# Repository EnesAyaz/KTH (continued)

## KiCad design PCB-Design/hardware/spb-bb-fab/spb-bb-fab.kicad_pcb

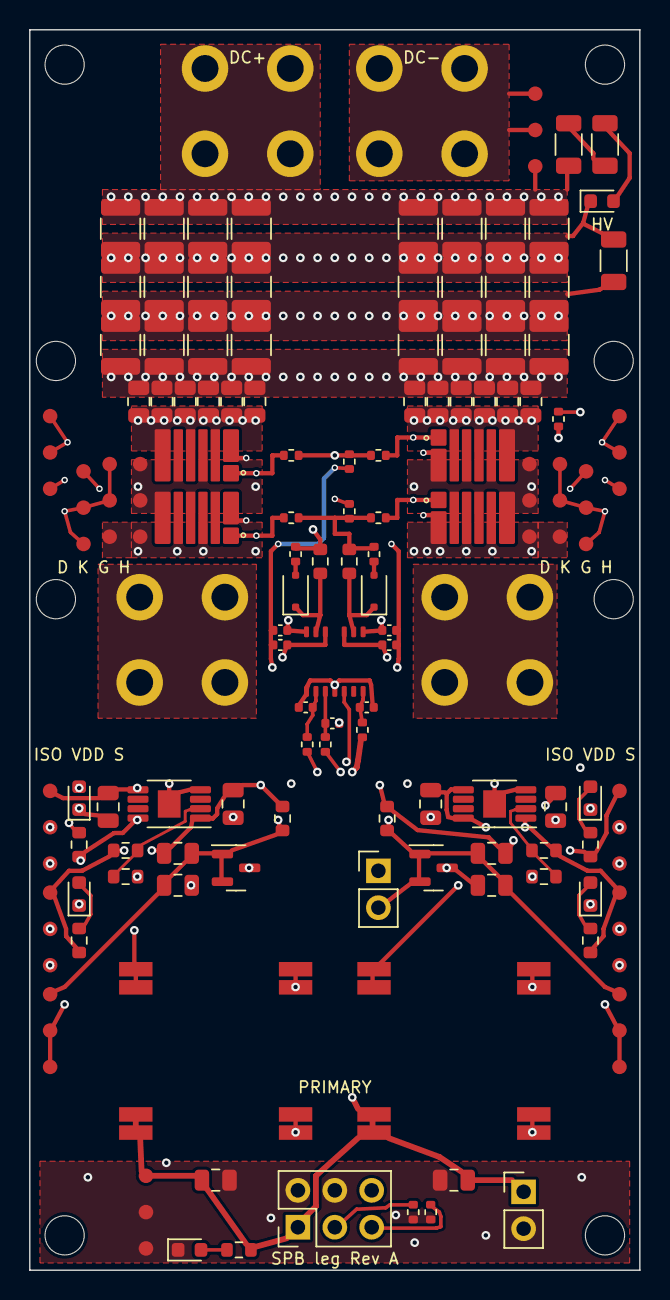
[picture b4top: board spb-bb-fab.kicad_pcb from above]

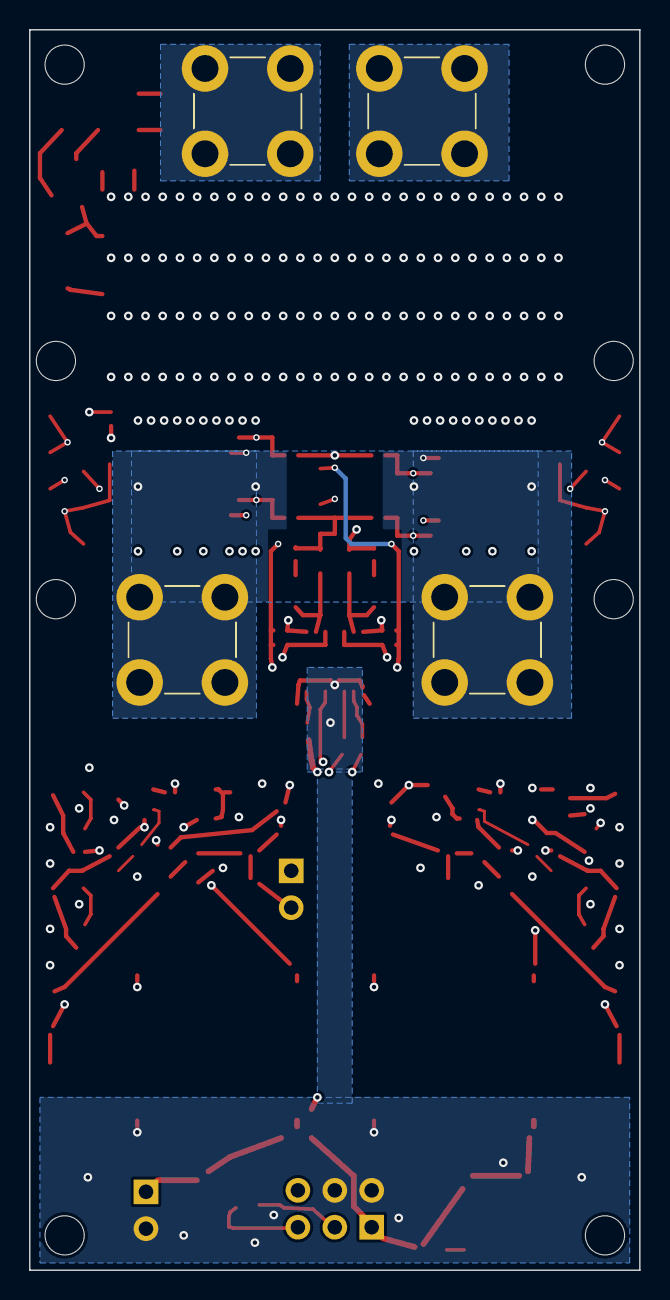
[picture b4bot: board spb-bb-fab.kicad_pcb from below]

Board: 4 copper layers, 42.0 x 85.4 mm, 134 parts (4 on the bottom side), 37 nets.

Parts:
C1, C2, C3, C4, C5, C6, C7, C8, C9, C10, C11, C12: 1uF 100V X7S; C_0805_2012Metric_TightCrtYd
C13, C14, C15, C16, C17, C18, C19, C20, C21, C22, C23, C24, C25, C26, C27, C28, C29, C30, C31, C32, C33, C34, C35, C36: 10uF 100V X7S; C_1210_3225Metric_TightCrtYd
C100, C101, C102, C103: 1uF 16V X7R 0402; C_0402_1005Metric
C104, C105: 100pF C0G 0402; C_0402_1005Metric
C106: 22nF 25V X7R 0402; C_0402_1005Metric
C107, C112: 4.7uF 25V X7R 0805; C_0805_2012Metric
C108, C113: 10uF 16V X7R 0805; C_0805_2012Metric
C109, C110, C114, C115: 4.7uF 16V X7R 0805; C_0805_2012Metric
C111, C116: 4.7uF 25V X7R 0805 (12 V in); C_0805_2012Metric
D1, D2: PMEG3020EJ; D_SOD-323F
D3: green 0603 (ISO A); LED_0603_1608Metric
D4: green 0603 (VDD A); LED_0603_1608Metric
D5: green 0603 (ISO B); LED_0603_1608Metric
D6: green 0603 (VDD B); LED_0603_1608Metric
D7: green 0603 (12 V); LED_0603_1608Metric
D8: red 0603 (DC link present); LED_0603_1608Metric
H1, H2, H3, H4: M2.5 insulated; MountingHole_2.7mm_M2.5
H5, H6, H7, H8: M2.5 heatsink; MountingHole_2.7mm_M2.5
HS1: Fischer LAM 4 K 50 12 + spreader; HS_LAM4K5012_assembly
J1: DC+; Wuerth_REDCUBE-THR_WP-THRBU_74650174_THR
J2: DC-; Wuerth_REDCUBE-THR_WP-THRBU_74650174_THR
J3, J4: AC; Wuerth_REDCUBE-THR_WP-THRBU_74650174_THR
J5: 1:+12V 2:GND 3:PWM_H 4:GND 5:PWM_L 6:DIS; PinHeader_2x03_P2.54mm_Vertical
J6: 1:NTC 2:DC- (LS domain!); PinHeader_1x02_P2.54mm_Vertical
J7: FAN 12V: 1 +12V, 2 GND; PinHeader_1x02_P2.54mm_Vertical
PS1, PS2: MGN1S1208MC; Murata_MGN1_SMD
Q1, Q2, Q3, Q4: EPC2361
R1: 0R5 1% (gate HL); R_0402_1005Metric
R2: 0R5 1% (gate HR); R_0402_1005Metric
R3: 0R5 1% (gate LL); R_0402_1005Metric
R4: 0R5 1% (gate LR); R_0402_1005Metric
R5: 0R75 1% (R_ON,A); R_0603_1608Metric
R6: 0R (R_OFF,A); R_0402_1005Metric
R7: 0R75 1% (R_ON,B); R_0603_1608Metric
R8: 0R (R_OFF,B); R_0402_1005Metric
R9: 47R 1% (INA); R_0402_1005Metric
R10: 47R 1% (INB); R_0402_1005Metric
R11: 3k 1% (RVDDI); R_0402_1005Metric
R12, R15: 102k 1%; R_0603_1608Metric
R13, R16: 23.7k 1%; R_0603_1608Metric
R14, R17: 2.2k 1% (shunt bias); R_0603_1608Metric
R30, R32: 2.7k (LED); R_0603_1608Metric
R31, R33: 1.8k (LED); R_0603_1608Metric
R34: 4.7k (LED); R_0603_1608Metric
R35: 10k (PWM_H pull-down); R_0402_1005Metric
R36: 10k (PWM_L pull-down); R_0402_1005Metric
R37, R38: 68k 1206 (HV LED); R_1206_3216Metric
R39: 100k 1206 (bleeder); R_1206_3216Metric
R41: 10k 1% (HS gate pull-down); R_0402_1005Metric
R42: 10k 1% (LS gate pull-down); R_0402_1005Metric
RT1: NTC 10k B3380; R_0402_1005Metric
TP1: D: Vds Q3; Probe_2Sig1Gnd_2.5_5.0
TP2: K: vKS Q3 (tip K); Probe_2Sig1Gnd_2.5_5.0
TP3: G: Vgs Q3; Probe_1Sig2Gnd_2.5_5.0
TP4: H: Vgs Q1 (iso); Probe_1Sig2Gnd_2.5_5.0
TP5: D: Vds Q4; Probe_2Sig1Gnd_2.5_5.0
TP6: K: vKS Q4 (tip K); Probe_2Sig1Gnd_2.5_5.0
TP7: G: Vgs Q4; Probe_1Sig2Gnd_2.5_5.0
TP8: H: Vgs Q2 (iso); Probe_1Sig2Gnd_2.5_5.0
TP9: ISO A; Probe_1Sig2Gnd_2.5_5.0
TP10: VDD A; Probe_1Sig2Gnd_2.5_5.0
TP11: S A; Probe_1Sig2Gnd_2.5_5.0
TP12: ISO B; Probe_1Sig2Gnd_2.5_5.0
TP13: VDD B; Probe_1Sig2Gnd_2.5_5.0
TP14: S B; Probe_1Sig2Gnd_2.5_5.0
TP15: 12V; Probe_1Sig2Gnd_2.5_5.0
TP16: DC link; Probe_1Sig2Gnd_2.5_5.0
U1: 2EDF7275K; 2EDF7275K_PG-TFLGA-13-4
U2, U3: TPS7A4901 6.29 V; HVSSOP-8-1EP_3x3mm_P0.65mm_EP1.57x1.89mm
U4, U5: TLV431A (1.24 V); SOT-23

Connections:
+12V: C111.1, C116.2, J5.1, J7.1, PS1.19, PS1.20, PS2.19, PS2.20, R11.1, R34.2, TP15.1
ADJA: R12.2, R13.1, U2.2
ADJB: R15.1, R16.2, U3.2
DCN: C1.2, C2.2, C3.2, C4.2, C5.2, C6.2, C7.2, C8.2, C9.2, C10.2, C11.2, C12.2, C13.1, C14.1, C15.1, C16.1, C17.1, C18.1, C19.1, C20.1, C21.2, C22.2, C23.2, C24.2, C25.2, C26.2, C27.2, C28.2, C29.1, C30.1, C31.1, C32.1, C33.1, C34.1, C35.1, C36.1, C102.2, C103.2, C114.1, C115.2, D8.1, J2.1, J6.2, Q3.2, Q3.4, Q3.6, Q4.2, Q4.4, Q4.6, R17.1, R39.2, R42.2, RT1.1, TP1.2, TP2.1, TP2.2, TP3.2, TP5.2, TP6.1, TP6.2, TP7.2, TP14.1, TP16.2, U5.1, U5.2
DCP: C1.1, C2.1, C3.1, C4.1, C5.1, C6.1, C7.1, C8.1, C9.1, C10.1, C11.1, C12.1, C13.2, C14.2, C15.2, C16.2, C17.2, C18.2, C19.2, C20.2, C21.1, C22.1, C23.1, C24.1, C25.1, C26.1, C27.1, C28.1, C29.2, C30.2, C31.2, C32.2, C33.2, C34.2, C35.2, C36.2, J1.1, Q1.3, Q1.5, Q1.7, Q2.3, Q2.5, Q2.7, R37.1, R39.1, TP16.1
DIS: J5.6, U1.5
GH_L: Q1.1, R1.1, TP4.1
GH_R: Q2.1, R2.2, TP8.1
GH_STAR: R1.2, R2.1, R5.2, R6.2, R41.2
GL_L: Q3.1, R3.1, TP3.1
GL_R: Q4.1, R4.2, TP7.1
GL_STAR: R3.2, R4.1, R7.2, R8.2, R42.1
GNDI: C104.1, C105.2, C106.2, C111.2, C116.1, D7.1, J5.2, J5.4, J7.2, PS1.1, PS1.2, PS2.1, PS2.2, R35.1, R36.1, TP15.2, U1.1, U1.4
HVA: R37.2, R38.1
HVB: D8.2, R38.2
INA: C104.2, R9.2, U1.2
INB: C105.1, R10.2, U1.3
ISOA_P: C107.2, PS1.11, PS1.12, R30.1, TP9.1, U2.5, U2.8
ISOB_P: C112.2, PS2.11, PS2.12, R32.1, TP12.1, U3.5, U3.8
LEDA_12V: D7.2, R34.1
LEDA_ISOA: D3.2, R30.2
LEDA_ISOB: D5.2, R32.2
LEDA_VDDA: D4.2, R31.2
LEDA_VDDB: D6.2, R33.2
NTC: J6.1, RT1.2
OFFA: D1.2, R6.1
OFFB: D2.2, R8.1
OUTA: D1.1, R5.1, U1.12
OUTB: D2.1, R7.1, U1.9
PWM_H: J5.3, R9.1, R35.2
PWM_L: J5.5, R10.1, R36.2
SW: C100.1, C101.1, C109.2, C110.1, J3.1, J4.1, Q1.2, Q1.4, Q1.6, Q2.2, Q2.4, Q2.6, Q3.3, Q3.5, Q3.7, Q4.3, Q4.5, Q4.7, R14.1, R41.1, TP1.1, TP4.2, TP5.1, TP8.2, TP11.1, U4.1, U4.2
VDDA: C100.2, C108.2, C109.1, R12.1, R14.2, R31.1, TP10.1, U1.13, U2.1
VDDB: C103.1, C113.2, C114.2, R15.2, R17.2, R33.1, TP13.1, U1.10, U3.1
VDDI: C106.1, R11.2, U1.7
VEEA: C101.2, C107.1, C108.1, C110.2, D3.1, D4.1, PS1.9, PS1.10, R13.2, TP9.2, TP10.2, TP11.2, U1.11, U2.4, U2.9, U4.3
VEEB: C102.1, C112.1, C113.1, C115.1, D5.1, D6.1, PS2.9, PS2.10, R16.1, TP12.2, TP13.2, TP14.2, U1.8, U3.4, U3.9, U5.3

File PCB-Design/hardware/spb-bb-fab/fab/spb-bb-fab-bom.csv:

Qty,References,Value,Footprint,Manufacturer part / note
4,Q1 Q3 Q2 Q4,EPC2361,EPC2361,EPC2361
12,C1 C2 C3 C4 C5 C6 C7 C8 C9 C10 C11 C12,1uF 100V X7S,C_0805_2012Metric_TightCrtYd,TDK C2012X7S2A105K125AB
24,C13 C14 C15 C16 C17 C18 C19 C20 C21 C22 C23 C24 C25 C26 C27 C28 C29 C30 C31 C32 C33 C34 C35 C36,10uF 100V X7S,C_1210_3225Metric_TightCrtYd,Murata GRM32EC72A106KE05L
4,R1 R2 R3 R4,0R5 1% (gate HL),R_0402_1005Metric,0.5R 0402 1% (Panasonic ERJ-2BQFR50X)
4,R41 R42 R35 R36,10k 1% (HS gate pull-down),R_0402_1005Metric,10k 0402 1%
1,U1,2EDF7275K,2EDF7275K_PG-TFLGA-13-4,Infineon 2EDF7275KXUMA1
2,R5 R7,"0R75 1% (R_ON,A)",R_0603_1608Metric,0.75R 0603 1% (Panasonic ERJ-3RQFR75V)
2,R6 R8,"0R (R_OFF,A)",R_0402_1005Metric,0R 0402 jumper (set R_OFF here)
2,D1 D2,PMEG3020EJ,D_SOD-323F,"Nexperia PMEG3020EJ (30 V, 2 A, SOD323F)"
4,C100 C101 C102 C103,1uF 16V X7R 0402,C_0402_1005Metric,Murata GRM155R71C105KA12
2,C104 C105,100pF C0G 0402,C_0402_1005Metric,Murata GRM1555C1H101JA01
1,C106,22nF 25V X7R 0402,C_0402_1005Metric,Murata GRM155R71E223KA61
2,R9 R10,47R 1% (INA),R_0402_1005Metric,47R 0402 1%
1,R11,3k 1% (RVDDI),R_0402_1005Metric,3.0k 0402 1%
2,PS1 PS2,MGN1S1208MC,Murata_MGN1_SMD,Murata MGN1S1208MC-R7
2,U2 U3,TPS7A4901 6.29 V,HVSSOP-8-1EP_3x3mm_P0.65mm_EP1.57x1.89mm,TI TPS7A4901DGNR
4,C107 C111 C112 C116,4.7uF 25V X7R 0805,C_0805_2012Metric,Murata GRM21BR71E475KA73
2,C108 C113,10uF 16V X7R 0805,C_0805_2012Metric,Murata GRM21BR71C106KE51
2,R12 R15,102k 1%,R_0603_1608Metric,102k 0603 1%
2,R13 R16,23.7k 1%,R_0603_1608Metric,23.7k 0603 1%
4,C109 C110 C114 C115,4.7uF 16V X7R 0805,C_0805_2012Metric,Murata GRM21BR71C475KA73
2,U4 U5,TLV431A (1.24 V),SOT-23,TI TLV431AIDBZR
2,R14 R17,2.2k 1% (shunt bias),R_0603_1608Metric,2.2k 0603 1%
4,J1 J2 J3 J4,DC+,Wuerth_REDCUBE-THR_WP-THRBU_74650174_THR,"Wuerth 74650174 (REDCUBE THR, M4)"
1,J5,1:+12V 2:GND 3:PWM_H 4:GND 5:PWM_L 6:DIS,PinHeader_2x03_P2.54mm_Vertical,2.54 mm header 2x3
1,J6,1:NTC 2:DC- (LS domain!),PinHeader_1x02_P2.54mm_Vertical,2.54 mm header 1x2
1,RT1,NTC 10k B3380,R_0402_1005Metric,Murata NCP15XH103F03RC
5,D3 D4 D5 D6 D7,green 0603 (ISO A),LED_0603_1608Metric,Wurth 150060GS75000
2,R30 R32,2.7k (LED),R_0603_1608Metric,2.7k 0603 1%
2,R31 R33,1.8k (LED),R_0603_1608Metric,1.8k 0603 1%
1,R34,4.7k (LED),R_0603_1608Metric,4.7k 0603 1%
1,J7,"FAN 12V: 1 +12V, 2 GND",PinHeader_1x02_P2.54mm_Vertical,2.54 mm header 1x2 (fan)
2,R37 R38,68k 1206 (HV LED),R_1206_3216Metric,68k 1206 1% 200 V
1,D8,red 0603 (DC link present),LED_0603_1608Metric,Wurth 150060RS75000
1,R39,100k 1206 (bleeder),R_1206_3216Metric,100k 1206 1% 200 V

Mechanical / thermal (not placed by the assembler)
1,HS1,"Fan heatsink 40x40x50 mm, 12 V fan",-,"Fischer Elektronik LAM 4 K 50 12 (0.65 K/W), Farnell 4708974"
1,HS1,"Heat spreader, Al 6061-T6, 42 x 14 x 3 mm, 2 pedestals 0.6 mm, 4 ears M2.5",-,"machined, drawing spb-bb-fab-spreader-drawing.pdf"
2,HS1,"Insulating gap pad over each cell, 8 x 10 mm, 0.5 mm, >= 5 W/mK",-,"Bergquist TGP 5000 (Gap Pad 5000S35) 0.020 in, cut to size, or equivalent"
1,HS1,Thermal compound spreader to heatsink,-,non-conductive silicone paste
4,H5-H8,M2.5 x 10 screw + insulating shoulder washer (heatsink),-,nylon or steel with insulating washer
4,H1-H4,M2.5 standoff + screw (board mounting),-,insulated
2,J1-J2,M4 screw for REDCUBE DC terminals,-,Wuerth WP-THRBU M4
2,J3-J4,M4 screw for REDCUBE AC terminals,-,Wuerth WP-THRBU M4

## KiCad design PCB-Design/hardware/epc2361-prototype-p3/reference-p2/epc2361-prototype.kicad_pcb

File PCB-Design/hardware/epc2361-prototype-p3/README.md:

# P3 — left-side DC input and gate driver

This revision supersedes P2 for placement review. It is not released for manufacturing.

## Implemented arrangement

85 × 55 mm, four layers. DC+ and DC− M4 terminals are on the upper left, with auxiliary power and HI/LI inputs on the left edge. AC is on the right. LMG1210 is immediately left of the switch group. Both switch pairs face left toward the driver. There are two EPC2361s per switch, four total.

Twenty-four TDK C2012X7S2A105K125AB bus capacitors are fitted: six above and six below each local half bridge. All are on the top face. Upper banks C1–C6 and C19–C24 directly serve the short local commutation paths; lower banks C7–C12 and C25–C30 supplement DC-link decoupling through the collectors. The count was increased so the lower row does not require a long top-layer positive feeder to the high-side devices. Nominal total is 24 µF; effective capacitance at 75 V and permissible RMS ripple have not been established.

Every component has a silkscreen reference. Gate/source headers are marked G and S; the control header has individual 12V/GND/HI/GND/LI/GND labels. DC and AC terminals and all five test points are identified. The BOM contains all 51 purchased components; five additional footprints are copper test points.

## Four-layer allocation

| Layer | Actual baseline P3 use |
|---|---|
| L1 / F.Cu | Components, local DC+/AC/DC− power islands, local gate escapes and decoupling |
| L2 / In1.Cu | Continuous DC− plane underneath the power cells; no routed signals |
| L3 / In2.Cu | DC+ collector, with auxiliary/control and source-return routes |
| L4 / B.Cu | AC collector and gate-drive routes |

L1 is not a whole-board DC+ plane. The commutation current passes through separate positive, switch-node and negative regions. L2 provides a nearby opposing current path. L3/L4 are already used for power distribution as well as driver connections; they are not two unused signal layers.

The gate-routing candidate adds explicit star branches and source-return corridors on the lower layers. Consult its separate report for its actual result before adopting it. A gate route over an unrelated DC+ plane is not automatically a properly referenced gate loop.

## Proposed stackup for fabricator review

F.Cu 0.070 mm / dielectric 0.100 mm / In1.Cu 0.035 mm / core 1.190 mm / In2.Cu 0.035 mm / dielectric 0.100 mm / B.Cu 0.070 mm. Copper plus dielectric totals 1.600 mm, excluding masks. The 0.100 mm outer dielectric spacing is a requested finished value, not a confirmed catalogue stackup. Manufacturer tolerances and 0.15 mm routing at the chosen finished copper weight must be accepted before ordering. Finish and assembly stencil remain unspecified.

## Inductance interpretation

Both primary upper-bank local geometries now share the same 6 mm device spacing and 0.100 mm top-to-return dielectric. The P2 selected external finger estimate (~0.385 nH) and six-capacitor ideal component ESL (~0.080 nH) apply only to those selected local contributions. Their ~0.47 nH subtotal is not the complete loop or a measured value. Lower-bank vias, shared collectors, package contributions and coupling require extraction; do not divide component ESL by all 24 capacitors and call that the switching-loop ESL.

## Electrical and mechanical release items

Design targets remain 75 V maximum, 36.7 A RMS / 51.9 A peak total output, 50 kHz nominal and 100 kHz maximum. Current capability and thermal rise have not been validated. The gate-routing report must demonstrate acceptable branch symmetry and source-return topology; DRC alone cannot do this. Current distribution through collectors and vias, MLCC bias/ripple, bootstrap operating range and actual gate overshoot also remain engineering checks.

The controller supplies nonoverlapping HI/LI in independent-input mode; bootstrap startup/refresh is required. JCTRL1 is not isolated. Gate headers must not be driven by a second active driver while onboard outputs are connected. Individual 0 Ω gate-resistor footprints remain for tuning and isolation.

Cold plate, insulating TIM, clamping force, mechanical mounting and cable-lug support are not designed. Tall headers and capacitors constrain the plate underside. No fabrication-ready claim is made while these remain open. Exact EPC2361 and LMG1210 manufacturer models are still unavailable: their local 3D models are explicitly approximate envelopes. Generic header and capacitor models require manufacturer-dimension comparison.

## Project files

Open epc2361-prototype-p3.kicad_pro; open its PCB and press Alt+3 for 3D. BOM.md / BOM.json are the revised component lists. The schematic and PCB use local footprints and local visualization models. connectivity-check.txt checks exported net assignments and model presence; drc.rpt records baseline geometric checks. A separate gate candidate is not the baseline released design. P2 files copied into this folder during preparation are historical; use only the P3-named project for this revision.

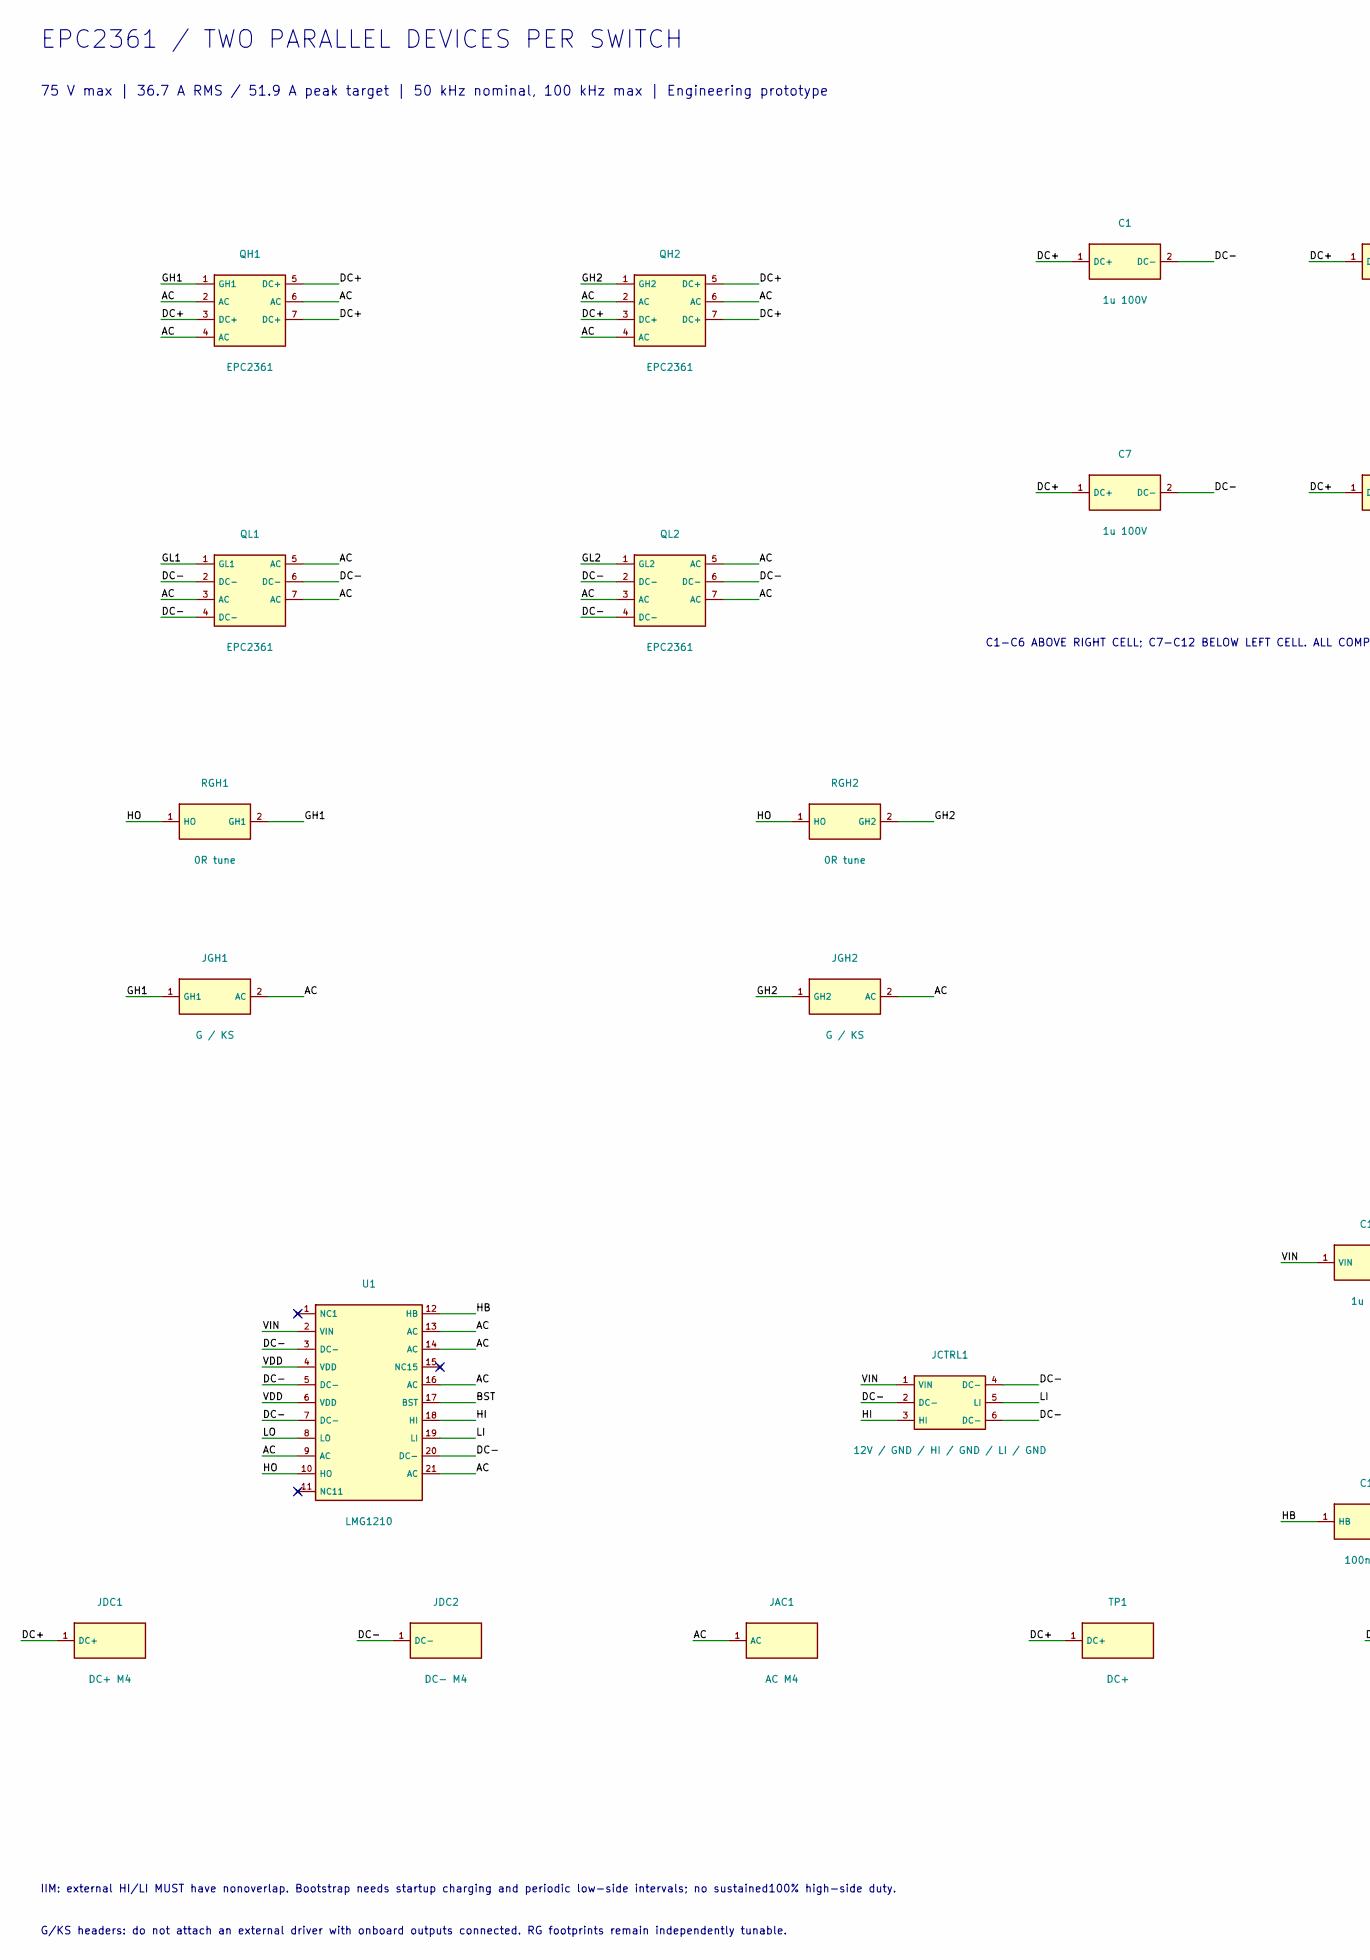
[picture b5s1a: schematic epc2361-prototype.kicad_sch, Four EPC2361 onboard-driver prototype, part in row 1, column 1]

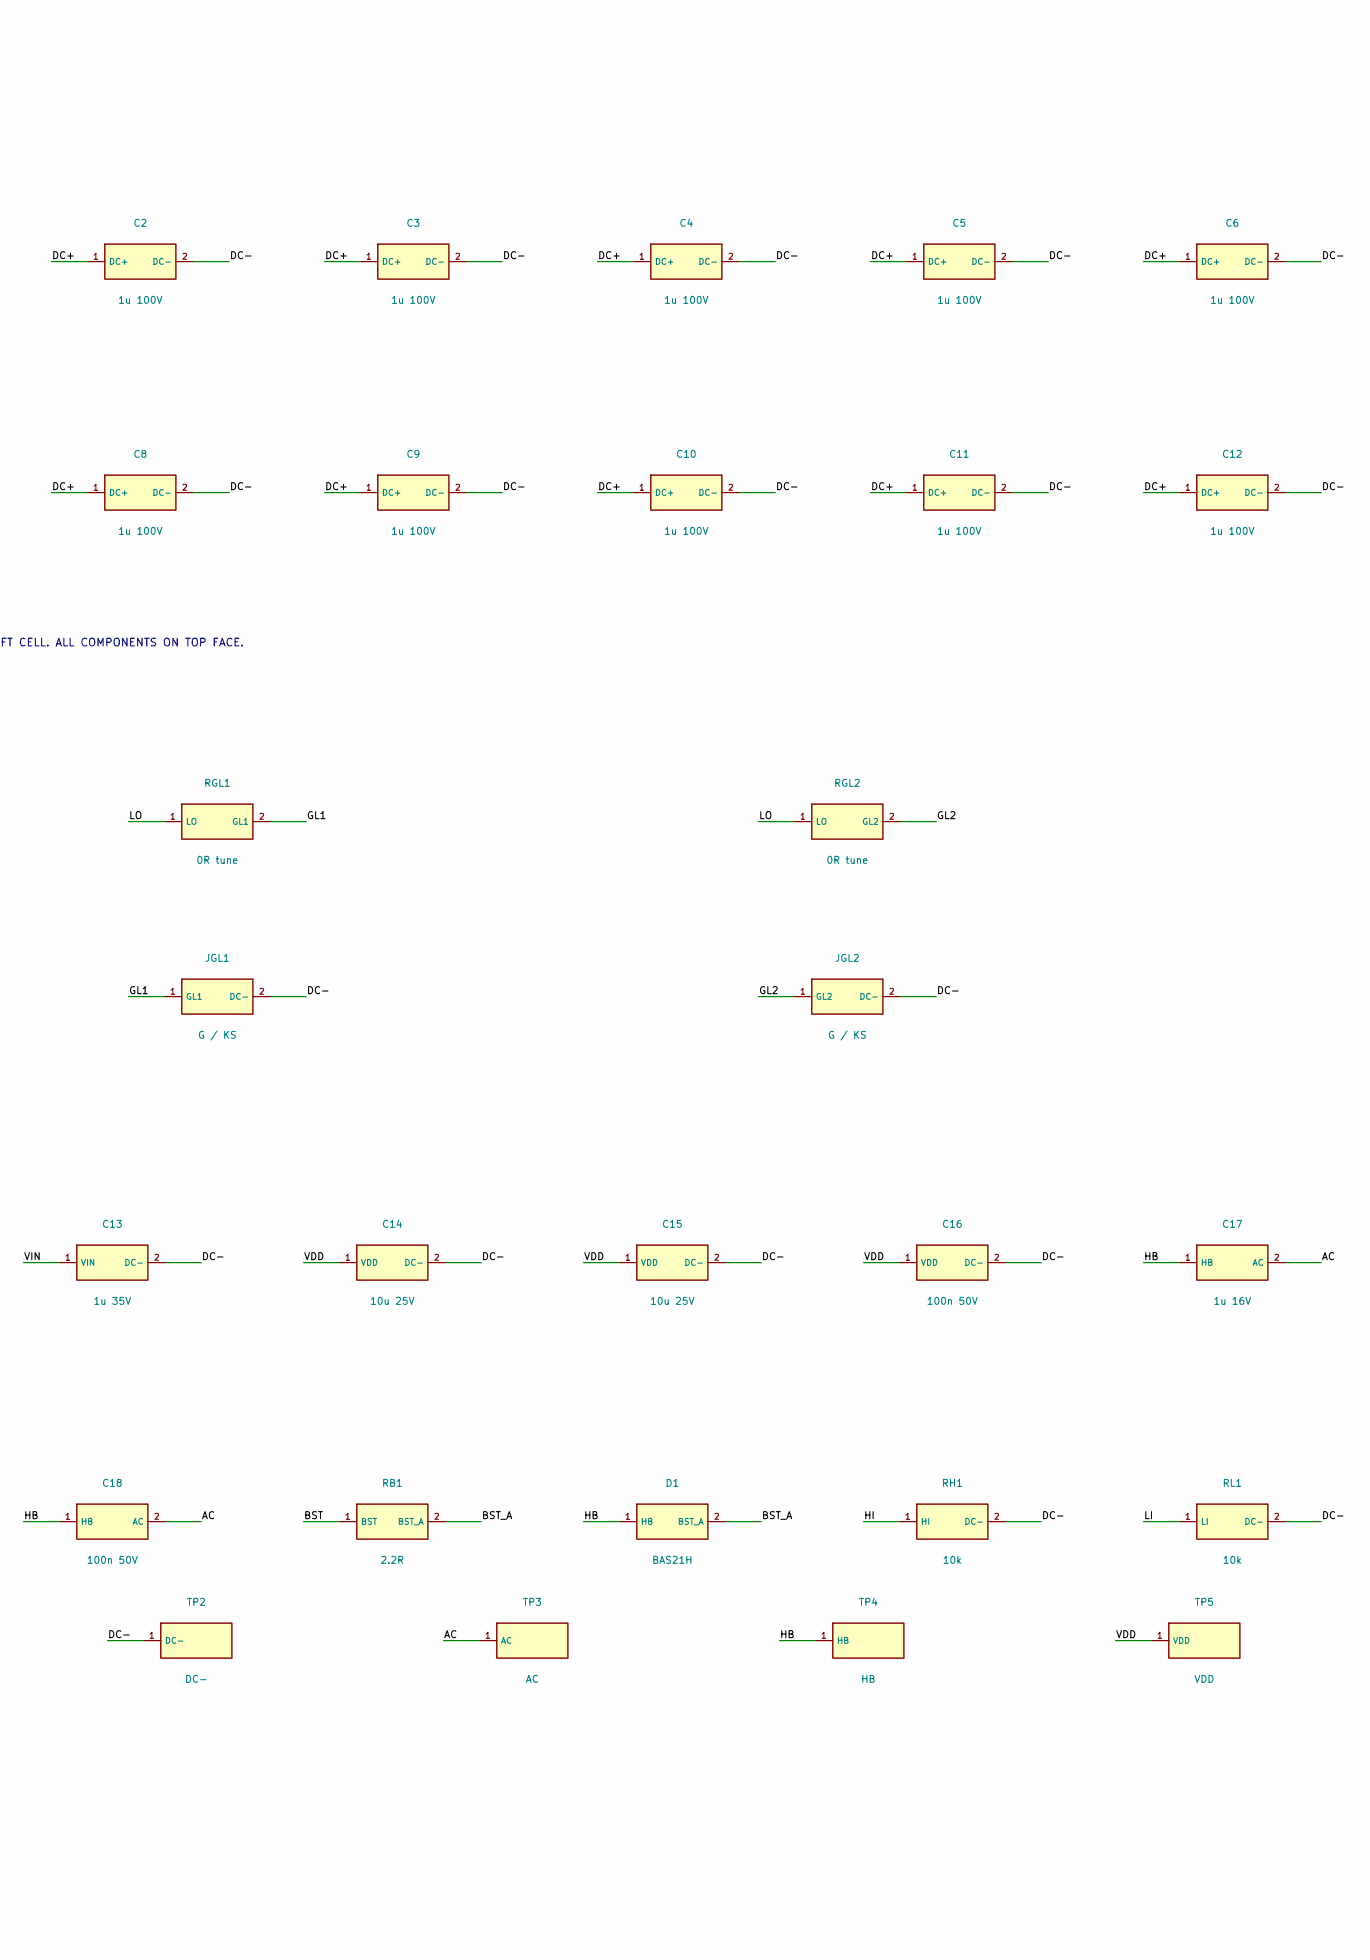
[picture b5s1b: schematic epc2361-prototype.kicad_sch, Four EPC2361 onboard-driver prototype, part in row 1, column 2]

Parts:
C1, C2, C3, C4, C5, C6, C7, C8, C9, C10, C11, C12: 1u 100V; C_0805_2012Metric
C13: 1u 35V; C_0603_1608Metric
C14, C15: 10u 25V; C_0805_2012Metric
C16, C18: 100n 50V; C_0603_1608Metric
C17: 1u 16V; C_0603_1608Metric
D1: BAS21H; D_SOD-123F
JAC1: AC M4; Wuerth_REDCUBE-THR_WP-THRBU_74650094_THR
JCTRL1: 12V / GND / HI / GND / LI / GND; PinHeader_1x06_P2.54mm_Vertical
JDC1: DC+ M4; Wuerth_REDCUBE-THR_WP-THRBU_74650094_THR
JDC2: DC- M4; Wuerth_REDCUBE-THR_WP-THRBU_74650094_THR
JGH1, JGH2: G / KS; PinHeader_1x02_P1.27mm_Vertical
JGL1, JGL2: G / KS; PinHeader_1x02_P1.27mm_Vertical
QH1, QH2: EPC2361
QL1, QL2: EPC2361
RB1: 2.2R; R_0603_1608Metric
RGH1, RGH2: 0R tune; R_0402_1005Metric
RGL1, RGL2: 0R tune; R_0402_1005Metric
RH1: 10k; R_0402_1005Metric
RL1: 10k; R_0402_1005Metric
TP1: DC+; Probe_Pad
TP2: DC-; Probe_Pad
TP3: AC; Probe_Pad
TP4: HB; Probe_Pad
TP5: VDD; Probe_Pad
U1: LMG1210; LMG1210_RVR

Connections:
AC: C17.2 (AC), C18.2 (AC), JAC1.1, JGH1.2 (AC), JGH2.2 (AC), QH1.2 (AC), QH1.4 (AC), QH1.6 (AC), QH2.2 (AC), QH2.4 (AC), QH2.6 (AC), QL1.3 (AC), QL1.5 (AC), QL1.7 (AC), QL2.3 (AC), QL2.5 (AC), QL2.7 (AC), TP3.1, U1.9 (AC), U1.13 (AC), U1.14 (AC), U1.16 (AC), U1.21 (AC)
BST: RB1.1 (BST), U1.17 (BST)
BST_A: D1.2 (BST_A), RB1.2 (BST_A)
DC+: C1.1 (DC+), C2.1 (DC+), C3.1 (DC+), C4.1 (DC+), C5.1 (DC+), C6.1 (DC+), C7.1 (DC+), C8.1 (DC+), C9.1 (DC+), C10.1 (DC+), C11.1 (DC+), C12.1 (DC+), JDC1.1, QH1.3 (DC+), QH1.5 (DC+), QH1.7 (DC+), QH2.3 (DC+), QH2.5 (DC+), QH2.7 (DC+), TP1.1
DC-: C1.2 (DC-), C2.2 (DC-), C3.2 (DC-), C4.2 (DC-), C5.2 (DC-), C6.2 (DC-), C7.2 (DC-), C8.2 (DC-), C9.2 (DC-), C10.2 (DC-), C11.2 (DC-), C12.2 (DC-), C13.2 (DC-), C14.2 (DC-), C15.2 (DC-), C16.2 (DC-), JCTRL1.2 (DC-), JCTRL1.4 (DC-), JCTRL1.6 (DC-), JDC2.1, JGL1.2 (DC-), JGL2.2 (DC-), QL1.2 (DC-), QL1.4 (DC-), QL1.6 (DC-), QL2.2 (DC-), QL2.4 (DC-), QL2.6 (DC-), RH1.2 (DC-), RL1.2 (DC-), TP2.1, U1.3 (DC-), U1.5 (DC-), U1.7 (DC-), U1.20 (DC-)
GH1: JGH1.1 (GH1), QH1.1 (GH1), RGH1.2 (GH1)
GH2: JGH2.1 (GH2), QH2.1 (GH2), RGH2.2 (GH2)
GL1: JGL1.1 (GL1), QL1.1 (GL1), RGL1.2 (GL1)
GL2: JGL2.1 (GL2), QL2.1 (GL2), RGL2.2 (GL2)
HB: C17.1 (HB), C18.1 (HB), D1.1 (HB), TP4.1, U1.12 (HB)
HI: JCTRL1.3 (HI), RH1.1 (HI), U1.18 (HI)
HO: RGH1.1 (HO), RGH2.1 (HO), U1.10 (HO)
LI: JCTRL1.5 (LI), RL1.1 (LI), U1.19 (LI)
LO: RGL1.1 (LO), RGL2.1 (LO), U1.8 (LO)
NC1: U1.1 (NC1)
NC11: U1.11 (NC11)
NC15: U1.15 (NC15)
VDD: C14.1 (VDD), C15.1 (VDD), C16.1 (VDD), TP5.1, U1.4 (VDD), U1.6 (VDD)
VIN: C13.1 (VIN), JCTRL1.1 (VIN), U1.2 (VIN)

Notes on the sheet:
EPC2361 / TWO PARALLEL DEVICES PER SWITCH
75 V max | 36.7 A RMS / 51.9 A peak target | 50 kHz nominal, 100 kHz max | Engineering prototype
C1-C6 ABOVE RIGHT CELL; C7-C12 BELOW LEFT CELL. ALL COMPONENTS ON TOP FACE.
IIM: external HI/LI MUST have nonoverlap. Bootstrap needs startup charging and periodic low-side intervals; no sustained100% high-side duty.
G/KS headers: do not attach an external driver with onboard outputs connected. RG footprints remain independently tunable.

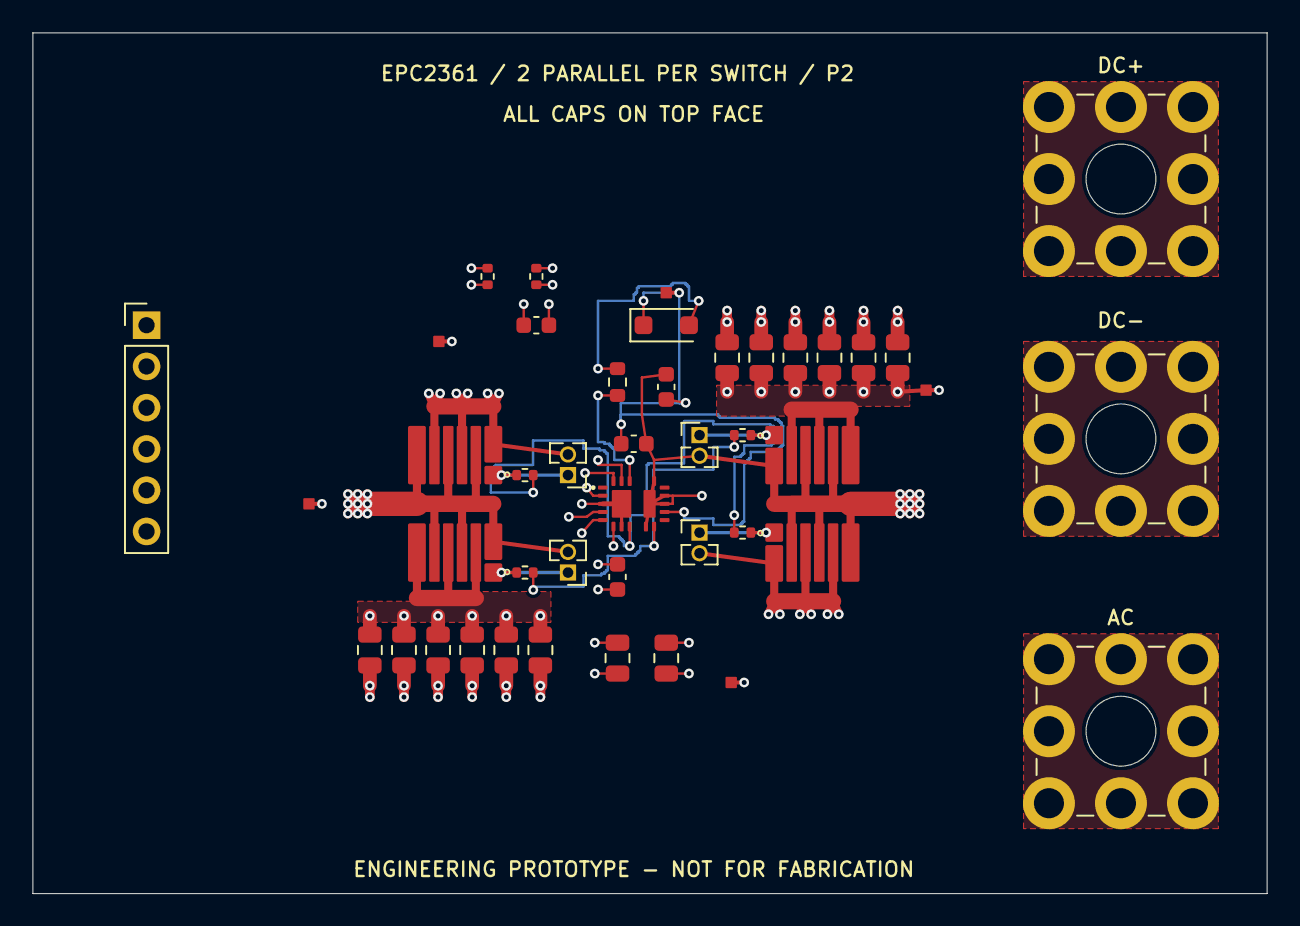
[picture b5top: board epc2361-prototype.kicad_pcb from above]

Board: 4 copper layers, 76.0 x 53.0 mm, 44 parts (0 on the bottom side), 16 nets.

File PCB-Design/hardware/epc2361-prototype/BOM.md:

# Prototype BOM

All quantities are for one four-FET board. Provisional engineering BOM; not purchasing release.

| References | Qty | MPN | Value | Footprint | Fit | Notes |
|---|---:|---|---|---|---|---|
| QH1, QL1, QH2, QL2 | 4 | EPC2361 | EPC2361 | epc2361-prototype:EPC2361 | Fit |  |
| C1, C2, C3, C4, C5, C6, C7, C8, C9, C10, C11, C12 | 12 | C2012X7S2A105K125AB | 1u 100V | Capacitor_SMD:C_0805_2012Metric | Fit |  |
| RGH1, RGL1, RGH2, RGL2 | 4 | RC0402JR-070RL | 0R tune | Resistor_SMD:R_0402_1005Metric | Fit | Individual gate damping footprint. Tune during double-pulse testing. |
| JGH1, JGL1, JGH2, JGL2 | 4 | FTS-102-01-L-S | G / KS | Connector_PinHeader_1.27mm:PinHeader_1x02_P1.27mm_Vertical | Fit | Measurement/external-drive header; never connect a second active driver. Remove local series resistor to isolate onboard output. Generic footprint: verify manufacturer drawing before release. |
| JDC1 | 1 | 74650094 | DC+ M4 | TerminalBlock_Wuerth:Wuerth_REDCUBE-THR_WP-THRBU_74650094_THR | Fit | 85 A maximum at20C is terminal-only; assembly/current path requires validation. 1.2Nm maximum specified torque. |
| JDC2 | 1 | 74650094 | DC- M4 | TerminalBlock_Wuerth:Wuerth_REDCUBE-THR_WP-THRBU_74650094_THR | Fit | 85 A maximum at20C is terminal-only; assembly/current path requires validation. 1.2Nm maximum specified torque. |
| JAC1 | 1 | 74650094 | AC M4 | TerminalBlock_Wuerth:Wuerth_REDCUBE-THR_WP-THRBU_74650094_THR | Fit | 85 A maximum at20C is terminal-only; assembly/current path requires validation. 1.2Nm maximum specified torque. |
| U1 | 1 | LMG1210RVRR | LMG1210 | epc2361-prototype:LMG1210_RVR | Fit | IIM: external nonoverlapping HI/LI; no internal shoot-through interlock in this mode. |
| JCTRL1 | 1 | TSW-106-07-G-S | 12V / GND / HI / GND / LI / GND | Connector_PinHeader_2.54mm:PinHeader_1x06_P2.54mm_Vertical | Fit |  |
| C13 | 1 | C1608X7R1V105K080AC | 1u 35V | Capacitor_SMD:C_0603_1608Metric | Fit | Verify effective capacitance and temperature; VDD X5R parts rated85C. |
| C14, C15 | 2 | C2012X5R1E106K125AB | 10u 25V | Capacitor_SMD:C_0805_2012Metric | Fit | Verify effective capacitance and temperature; VDD X5R parts rated85C. |
| C16, C18 | 2 | C1608X7R1H104K080AA | 100n 50V | Capacitor_SMD:C_0603_1608Metric | Fit | Verify effective capacitance and temperature; VDD X5R parts rated85C. |
| C17 | 1 | C1608X7R1C105K080AC | 1u 16V | Capacitor_SMD:C_0603_1608Metric | Fit | Verify effective capacitance and temperature; VDD X5R parts rated85C. |
| RB1 | 1 | RC0603FR-072R2L | 2.2R | Resistor_SMD:R_0603_1608Metric | Fit |  |
| D1 | 1 | BAS21H,115 | BAS21H | Diode_SMD:D_SOD-123F | Fit | External bootstrap diode: cathode HB, anode BST_A. Not a bootstrap voltage clamp. |
| RH1, RL1 | 2 | RC0402FR-0710KL | 10k | Resistor_SMD:R_0402_1005Metric | Fit |  |
| TP1 | 1 | PCB copper test pad | DC+ | epc2361-prototype:Probe_Pad | Fit | PCB feature; no purchased component. |
| TP2 | 1 | PCB copper test pad | DC- | epc2361-prototype:Probe_Pad | Fit | PCB feature; no purchased component. |
| TP3 | 1 | PCB copper test pad | AC | epc2361-prototype:Probe_Pad | Fit | PCB feature; no purchased component. |
| TP4 | 1 | PCB copper test pad | HB | epc2361-prototype:Probe_Pad | Fit | PCB feature; no purchased component. |
| TP5 | 1 | PCB copper test pad | VDD | epc2361-prototype:Probe_Pad | Fit | PCB feature; no purchased component. |
